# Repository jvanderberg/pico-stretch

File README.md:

# Pico Stretch

This is an RP2350B Dev board that breaks out all 48 GPIO pins.

It follows the original footprint of the RP2040 dev board, but adds 12 pins on each side.

Pinout:

```
1	GPIO0	        64	VBUS
2	GPIO1	        63	VSYS
3	GND	            62	GND
4	GPIO2	        61	3v3
5	GPIO3	        60	3v3_EN
6	GPIO4	        59	ADC_VREF
7	GPIO5	        58	GPIO28
8	GND	            57	GND
9	GPIO6	        56	GPIO27
10	GPIO7	        55	GPIO26
11	GPIO8	        54	RUN
12	GPIO9	        53	GPIO22
13	GND 	        52	GND
14	GPIO10	        51	GPIO21
15	GPIO11	        50	GPIO20
16	GPIO12	        49	GPIO19
17	GPIO13	        48	GPIO18
18	GND	            47	GND
19	GPIO14	        46	GPIO17
20	GPIO15	        45	GPIO16
21	GPIO23	        44	GPIO47/ADC7
22	GPIO24          43	GPIO46/ADC6
23	GPIO25	        42	GPIO45/ADC5
24	GPIO29	        41	GPIO44/ADC4
25	GPIO30	        40	GPIO43/ADC3
26	GPIO31	        39	GPIO42/ADC2
27	GPIO32	        38	GPIO41/ADC1
28	GPIO33	        37	GPIO40/ADC0
29	GPIO34	        36	GPIO39
30	GPIO35	        35	GPIO38
31  GND             34  GND
32  GPIO36          33  GPIO37
```

## Production files for JLCPCB

The production files for JLCPCB are in the 'production' directory.

pico-stretch.zip is the zipped Gerber files.

bom.csv and positions.csv are the Bill of materials and placements files respectively.

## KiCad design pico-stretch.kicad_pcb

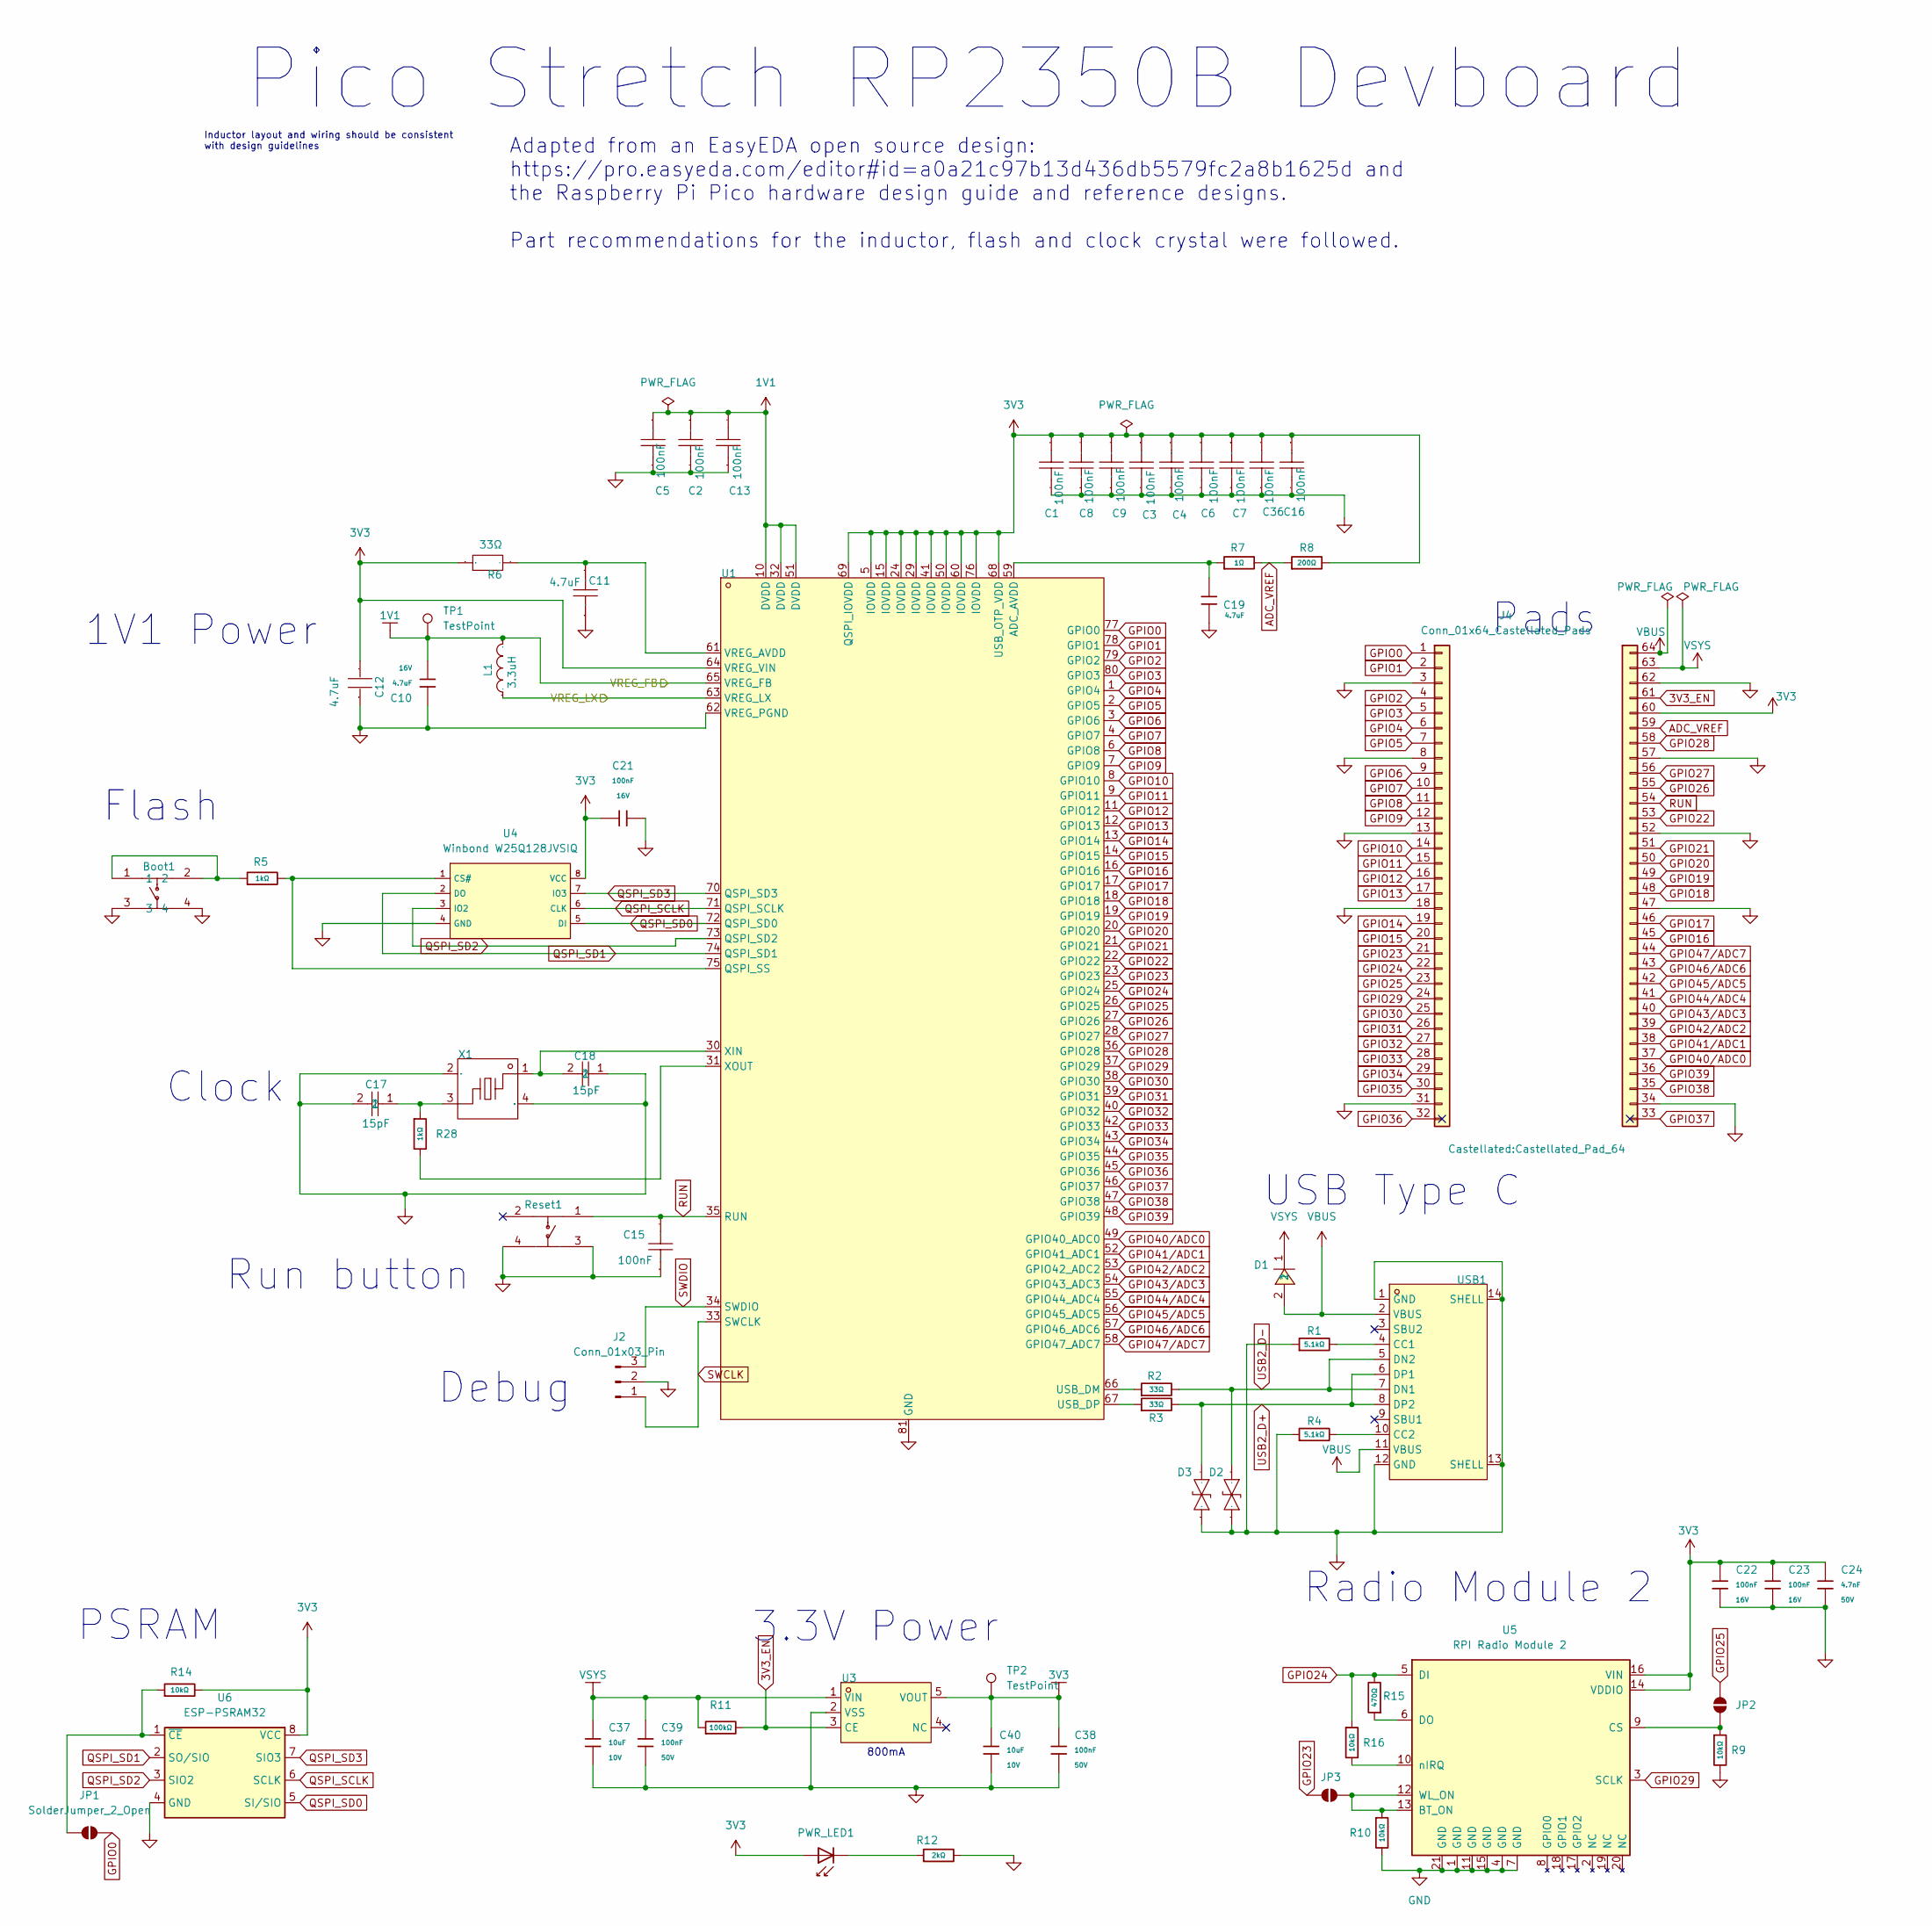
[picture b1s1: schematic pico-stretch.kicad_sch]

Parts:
Boot1: K2-1808SN-A4SW-01; KEY-SMD_4P-L4.2-W3.2-P2.20-LS5.1-TL; Manufacturer Part K2-1808SN-A4SW-01; LCSC Part Name 4.2mm*3.25mm
C1, C2, C3, C4, C5, C6, C7, C8, C13, C16, C36: 100nF; C0402; Manufacturer Part CL05B104KO5NNNC; LCSC Part Name 100nF ±10% 16V
C9, C15: 100nF; C0402; Voltage Rating 50V; Manufacturer Part CC0603KRX7R9BB104; LCSC Part Name 100nF ±10% 50V
C10: 4.7uF; C_0603; Voltage Rated 16V; Tolerance ±10%; Part CL10A475KO8NNNC; LCSC C19666
C11: 4.7uF; Manufacturer Part CL05A475MP5NRNC; LCSC Part Name 4.7uF ±20% 10V
C12: 4.7uF; Manufacturer Part CL10A475KO8NNNC; LCSC Part Name 4.7uF ±10% 16V
C17, C18: 15pF; C0402; Manufacturer Part 0402CG150J500NT; LCSC Part Name 15pF ±5% 50V
C19: 4.7uF; C_0402; Voltage Rated 10V; Tolerance ±20%; Part CL05A475MP5NRNC; LCSC C23733
C21, C22, C23: 100nF; C_0402; Voltage Rated 16V; Tolerance ±10%; Part CL05B104KO5NNNC; LCSC C1525
C24: 4.7nF; C_0603; Voltage Rated 50V; Tolerance ±10%; Part 0603B472K500NT; LCSC C53987
C37, C40: 10uF; C_0603; Voltage Rated 10V; Tolerance ±10%; Part CL10A106KP8NNNC; LCSC C19702
C38, C39: 100nF; C_0603; Voltage Rated 50V; Tolerance ±10%; Part CC0603KRX7R9BB104; LCSC C14663
D1: POWERDI-123_L2.8-W1.8-LS3.7-RD; Manufacturer Part DFLS130L-7; LCSC Part Name 电压:30V 电流:1A
D2, D3: RCLAMP0521P.TCT-MS; D0402-BI; Manufacturer Part RCLAMP0521P.TCT-MS; LCSC Part Name 双向TVS 5V截止 4A峰值脉冲 丝印N
J2: Conn_01x03_Pin; PinHeader_1x03_P2.54mm_Vertical
J4: Conn_01x64_Castellated_Pads; Castellated_Pad_64
JP1, JP2, JP3: SolderJumper_2_Open; SolderJumper-2_P1.3mm_Open_Pad1.0x1.5mm
L1: IND-SMD_L2.0-W1.6_AOTA-B201610S3R3-101-T; Manufacturer Part AOTA-B201610S3R3-101-T; LCSC Part Name AOTA-B201610S3R3-101-T
PWR_LED1: Red; D_0603; Part KT-0603R; LCSC C2286
R1, R4: 5.1kΩ; R_0402; Overload Voltage (Max) 50V; Tolerance ±1%; Part 0402WGF5101TCE; LCSC C25905
R2, R3: 33Ω; R_0402; Overload Voltage (Max) 50V; Tolerance ±1%; Part 0402WGF330JTCE; LCSC C25105
R5: 1kΩ; R_0402; Overload Voltage (Max) 50V; Tolerance ±1%; Part 0402WGF1001TCE; LCSC C11702
R6: 33Ω; R0402; Manufacturer Part 0402WGF330JTCE; LCSC Part Name 33Ω ±1% 62.5mW 厚膜电阻
R7: 1Ω; R_0603; Overload Voltage (Max) 75V; Tolerance ±1%; Part 0603WAF100KT5E; LCSC C22936
R8: 200Ω; R_0603; Overload Voltage (Max) 75V; Tolerance ±1%; Part 0603WAF2000T5E; LCSC C8218
R9, R10, R14, R16: 10kΩ; R_0402; Overload Voltage (Max) 50V; Tolerance ±1%; Part 0402WGF1002TCE; LCSC C25744
R11: 100kΩ; R_0402; Overload Voltage (Max) 50V; Tolerance ±1%; Part 0402WGF1003TCE; LCSC C25741
R12: 2kΩ; R_0402; Overload Voltage (Max) 50V; Tolerance ±1%; Part 0402WGF2001TCE; LCSC C4109
R15: 470Ω; R_0402; Overload Voltage (Max) 50V; Tolerance ±1%; Part 0402WGF4700TCE; LCSC C25117
R28: 1kΩ; R_0603; Overload Voltage (Max) 75V; Tolerance ±1%; Part 0603WAF1001T5E; LCSC C21190
Reset1: K2-1808SN-A4SW-01; KEY-SMD_4P-L4.2-W3.2-P2.20-LS5.1-TL; Manufacturer Part K2-1808SN-A4SW-01; LCSC Part Name 4.2mm*3.25mm
TP1, TP2: TestPoint; TestPoint_Pad_1.0x1.0mm
U1: QFN-80_L10.0-W10.0-P0.40-TL-EP3.4; Manufacturer Part RP2350B; LCSC Part Name RP2350B
U3: SOT-23-5_L3.0-W1.7-P0.95-LS2.8-BR; Manufacturer Part ME6217C33M5G; LCSC Part Name ME6217C33M5G
U4: Winbond W25Q128JVSIQ; SOIC-8_L5.3-W5.3-P1.27-LS8.0-BL; Part W25Q128JVSIQ; LCSC C97521
U5: RPI Radio Module 2; rpi_rmc20452t
U6: ESP-PSRAM32; SOIC-8_3.9x4.9mm_P1.27mm
USB1: USB-C-SMD_TYPE-C-6PIN-2MD-073; Manufacturer Part TYPE-C 16PIN 2MD(073); LCSC Part Name Type-C 母 卧贴
X1: Manufacturer Part ABM8-272-T3; LCSC Part Name ABM8-272-T3

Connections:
1V1: C2.1, C5.1, C10.2, C13.2, L1.2, TP1.1, U1.10 (DVDD), U1.32 (DVDD), U1.51 (DVDD), U1.65 (VREG_FB)
3V3: C1.1, C3.1, C4.1, C6.1, C7.1, C8.2, C9.2, C12.2, C16.1, C21.1, C22.1, C23.1, C24.1, C36.2, C38.1, C40.1, J4.60, PWR_LED1.2, R6.1, R8.2, R14.2, TP2.1, U1.5 (IOVDD), U1.15 (IOVDD), U1.24 (IOVDD), U1.29 (IOVDD), U1.41 (IOVDD), U1.50 (IOVDD), U1.60 (IOVDD), U1.64 (VREG_VIN), U1.68 (USB_OTP_VDD), U1.69 (QSPI_IOVDD), U1.76 (IOVDD), U3.5 (VOUT), U4.8 (VCC), U5.14 (VDDIO), U5.16 (VIN), U6.8 (VCC)
3V3_EN: J4.61, R11.2, U3.3 (CE)
/VREG_LX: L1.1, U1.63 (VREG_LX)
ADC_VREF: J4.59, R7.2, R8.1
GND: Boot1.3, Boot1.4, C1.2, C2.2, C3.2, C4.2, C5.2, C6.2, C7.2, C8.1, C9.1, C10.1, C11.1, C12.1, C13.1, C15.1, C16.2, C17.2, C18.1, C19.2, C21.2, C22.2, C23.2, C24.2, C36.1, C37.2, C38.2, C39.2, C40.2, D2.1, D3.1, J2.2, J4.3, J4.8, J4.13, J4.18, J4.31, J4.34, J4.47, J4.52, J4.57, J4.62, R1.1, R4.1, R9.2, R10.2, R12.2, Reset1.3, Reset1.4, U1.62 (VREG_PGND), U1.81 (GND), U3.2 (VSS), U4.4 (GND), U5.1 (GND), U5.4 (GND), U5.7 (GND), U5.11 (GND), U5.15 (GND), U5.21 (GND), U6.4 (GND), USB1.1 (GND), USB1.12 (GND), USB1.13 (SHELL), USB1.14 (SHELL), X1.2 (GND), X1.4 (GND)
GPIO0: J4.1, JP1.2 (B), U1.77 (GPIO0)
GPIO1: J4.2, U1.78 (GPIO1)
GPIO2: J4.4, U1.79 (GPIO2)
GPIO3: J4.5, U1.80 (GPIO3)
GPIO4: J4.6, U1.1 (GPIO4)
GPIO5: J4.7, U1.2 (GPIO5)
GPIO6: J4.9, U1.3 (GPIO6)
GPIO7: J4.10, U1.4 (GPIO7)
GPIO8: J4.11, U1.6 (GPIO8)
GPIO9: J4.12, U1.7 (GPIO9)
GPIO10: J4.14, U1.8 (GPIO10)
GPIO11: J4.15, U1.9 (GPIO11)
GPIO12: J4.16, U1.11 (GPIO12)
GPIO13: J4.17, U1.12 (GPIO13)
GPIO14: J4.19, U1.13 (GPIO14)
GPIO15: J4.20, U1.14 (GPIO15)
GPIO16: J4.45, U1.16 (GPIO16)
GPIO17: J4.46, U1.17 (GPIO17)
GPIO18: J4.48, U1.18 (GPIO18)
GPIO19: J4.49, U1.19 (GPIO19)
GPIO20: J4.50, U1.20 (GPIO20)
GPIO21: J4.51 (Pin_61), U1.21 (GPIO21)
GPIO22: J4.53, U1.22 (GPIO22)
GPIO23: J4.21, JP3.1 (A), U1.23 (GPIO23)
GPIO24: J4.22, R15.2, R16.1, U1.25 (GPIO24), U5.5 (DI)
GPIO25: J4.23, JP2.2 (B), U1.26 (GPIO25)
GPIO26: J4.55, U1.27 (GPIO26)
GPIO27: J4.56, U1.28 (GPIO27)
GPIO28: J4.58, U1.36 (GPIO28)
GPIO29: J4.24, U1.37 (GPIO29), U5.3 (SCLK)
GPIO30: J4.25, U1.38 (GPIO30)
GPIO31: J4.26, U1.39 (GPIO31)
GPIO32: J4.27, U1.40 (GPIO32)
GPIO33: J4.28, U1.42 (GPIO33)
GPIO34: J4.29, U1.43 (GPIO34)
GPIO35: J4.30, U1.44 (GPIO35)
GPIO36: J4.32, U1.45 (GPIO36)
GPIO37: J4.33, U1.46 (GPIO37)
GPIO38: J4.35, U1.47 (GPIO38)
GPIO39: J4.36, U1.48 (GPIO39)
GPIO40/ADC0: J4.37, U1.49 (GPIO40_ADC0)
GPIO41/ADC1: J4.38, U1.52 (GPIO41_ADC1)
GPIO42/ADC2: J4.39, U1.53 (GPIO42_ADC2)
GPIO43/ADC3: J4.40, U1.54 (GPIO43_ADC3)
GPIO44/ADC4: J4.41, U1.55 (GPIO44_ADC4)
GPIO45/ADC5: J4.42, U1.56 (GPIO45_ADC5)
GPIO46/ADC6: J4.43, U1.57 (GPIO46_ADC6)
GPIO47/ADC7: J4.44, U1.58 (GPIO47_ADC7)
unnamed: Boot1.1, Boot1.2, R5.1
unnamed: C17.1, R28.1, X1.3
unnamed: JP1.1 (A), R14.1, U6.1 (~CE)
unnamed: JP2.1 (A), R9.1, U5.9 (CS)
unnamed: JP3.2 (B), R10.1, U5.12 (WL_ON), U5.13 (BT_ON)
unnamed: PWR_LED1.1, R12.1
unnamed: C19.1, R7.1, U1.59 (ADC_AVDD)
unnamed: R5.2, U1.75 (QSPI_SS), U4.1 (CS#)
unnamed: R2.1, U1.66 (USB_DM)
unnamed: R3.1, U1.67 (USB_DP)
unnamed: C11.2, R6.2, U1.61 (VREG_AVDD)
unnamed: C18.2, U1.30 (XIN), X1.1
unnamed: R28.2, U1.31 (XOUT)
unnamed: R15.1, U5.6 (DO)
unnamed: R16.2, U5.10 (nIRQ)
unnamed: R1.2, USB1.4 (CC1)
unnamed: R4.2, USB1.10 (CC2)
QSPI_SCLK: U1.71 (QSPI_SCLK), U4.6 (CLK), U6.6 (SCLK)
QSPI_SD0: U1.72 (QSPI_SD0), U4.5 (DI), U6.5 (SI/SIO)
QSPI_SD1: U1.74 (QSPI_SD1), U4.2 (DO), U6.2 (SO/SIO)
QSPI_SD2: U1.73 (QSPI_SD2), U4.3 (IO2), U6.3 (SIO2)
QSPI_SD3: U1.70 (QSPI_SD3), U4.7 (IO3), U6.7 (SIO3)
RUN: C15.2, J4.54, Reset1.1, U1.35 (RUN)
SWCLK: J2.1, U1.33 (SWCLK)
SWDIO: J2.3, U1.34 (SWDIO)
USB2_D+: D3.2, R3.2, USB1.6 (DP1), USB1.8 (DP2)
USB2_D-: D2.2, R2.2, USB1.5 (DN2), USB1.7 (DN1)
VBUS: D1.2, J4.64, USB1.2 (VBUS), USB1.11 (VBUS)
VSYS: C37.1, C39.1, D1.1, J4.63, R11.1, U3.1 (VIN)

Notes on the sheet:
Clock
PSRAM
USB Type C
Flash
3.3V Power
Radio Module 2
Debug
Run button
Pico Stretch RP2350B Devboard
Inductor layout and wiring should be consistent with design guidelines
1V1 Power
Pads
Adapted from an EasyEDA open source design: https://pro.easyeda.com/editor#id=a0a21c97b13d436db5579fc2a8b1625d and the Raspberry Pi Pico hardware design guide and reference designs. Part recommendations for the inductor, flash and clock crystal were followed.
800mA

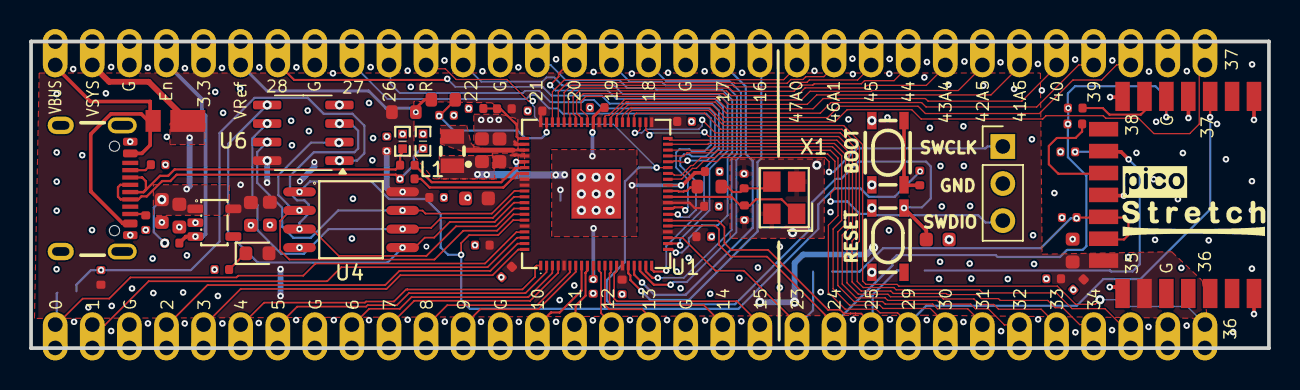
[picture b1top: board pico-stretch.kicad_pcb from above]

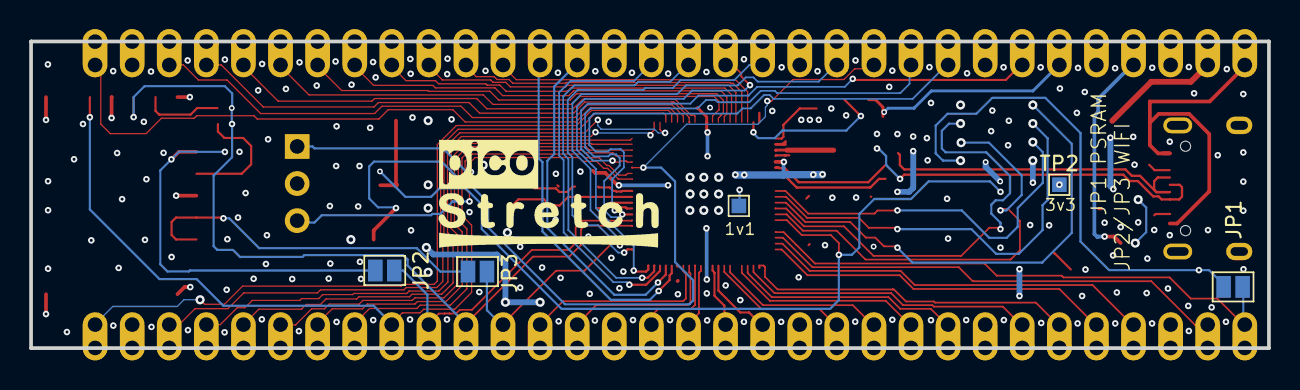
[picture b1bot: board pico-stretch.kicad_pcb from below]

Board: 4 copper layers, 84.8 x 21.0 mm, 64 parts (5 on the bottom side), 83 nets.

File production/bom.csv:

Designator,Footprint,Quantity,Value,LCSC Part #
"BOOT1, RESET1",KEY-SMD_4P-L4.2-W3.2-P2.20-LS5.1-TL,2,K2-1808SN-A4SW-01,C92589
"C1, C13, C16, C2, C21, C22, C23, C36, C7, C8",C_0402,10,100nF,C1525
"C10, C12",C_0603,2,4.7uF,C19666
"C11, C19",C_0402,2,4.7uF,C23733
"C15, C38, C39, C9",C_0603,4,100nF,C14663
"C17, C18",C_0402,2,15pF,C1548
C24,C_0603,1,4.7nF,C53987
"C3, C4, C5, C6",C_0402,4,100nF,
"C37, C40",C_0603,2,10uF,C19702
D1,POWERDI-123_L2.8-W1.8-LS3.7-RD,1,~,C110493
"D2, D3",D0402-BI,2,RCLAMP0521P.TCT-MS,C3029033
J2,PinHeader_1x03_P2.54mm_Vertical,1,Conn_01x03_Pin,
J4,Castellated_Pad_64,1,Conn_01x64_Castellated_Pads,
L1,IND-SMD_L2.0-W1.6_AOTA-B201610S3R3-101-T,1,~,C42411119
PWR_LED1,D_0603,1,Red,C2286
"R1, R4",R_0402,2,5.1kΩ,C25905
"R10, R14, R16, R9",R_0402,4,10kΩ,C25744
R11,R_0402,1,100kΩ,C25741
R12,R_0402,1,2kΩ,C4109
R15,R_0402,1,470Ω,C25117
"R2, R3, R6",R_0402,3,33Ω,C25105
R28,R_0603,1,1kΩ,C21190
R5,R_0402,1,1kΩ,C11702
R7,R_0603,1,1Ω,C22936
R8,R_0603,1,200Ω,C8218
"TP1, TP2",TestPoint_Pad_1.0x1.0mm,2,TestPoint,
U1,QFN-80_L10.0-W10.0-P0.40-TL-EP3.4,1,~,C42415655
U3,SOT-23-5_L3.0-W1.7-P0.95-LS2.8-BR,1,~,C427602
U4,SOIC-8_L5.3-W5.3-P1.27-LS8.0-BL,1,Winbond W25Q128JVSIQ,C97521
U5,rpi_rmc20452t,1,RPI Radio Module 2,
U6,SOIC-8_3.9x4.9mm_P1.27mm,1,ESP-PSRAM32,
USB1,USB-C-SMD_TYPE-C-6PIN-2MD-073,1,~,C2765186
X1,CRYSTAL-SMD_4P-L3.2-W2.5-BL,1,~,C20625731

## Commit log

2025-06-16 Push first version
2025-06-16 Remove lock files
2025-06-16 Update gitignore
2025-06-16 Remove old library
2025-06-16 Small changes
2025-06-17 Re-did schematic
2025-06-17 Remove backups
2025-06-17 Updated git ignore
2025-06-18 Updated footprints, more basic parts
2025-06-18 Update gitignore to ignore backup directory
2025-07-07 Added wifi and PSRAM
2025-07-10 Super version
2025-08-06 Cleanup
2025-08-06 final cleanup
2025-08-06 Cleanup of connectors
2025-09-17 Before RM2 reset
2025-09-18 Renames and doc updates
2025-09-18 .gitignore cleanup
2025-09-18 Fixes, 3v3 front pour, change to signal/gnd/gnd/signal stackup
2025-09-19 Updated production bom, positions, gerbers
2025-09-19 Minor text update
2025-09-19 Fixes after review
2025-09-20 Fixed vias
2025-09-20 New production vias
2025-10-31 Major re-work for castellated pads and PSRAM on top
2025-10-31 Going to prod
2025-11-28 Updated labels and production files
